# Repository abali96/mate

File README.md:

# mate

Desktop display for live stock market, time, and weather data on a scrolling LED matrix. See http://arjunbali.com/#mate for a full description of the tech, a photo gallery, and a video!

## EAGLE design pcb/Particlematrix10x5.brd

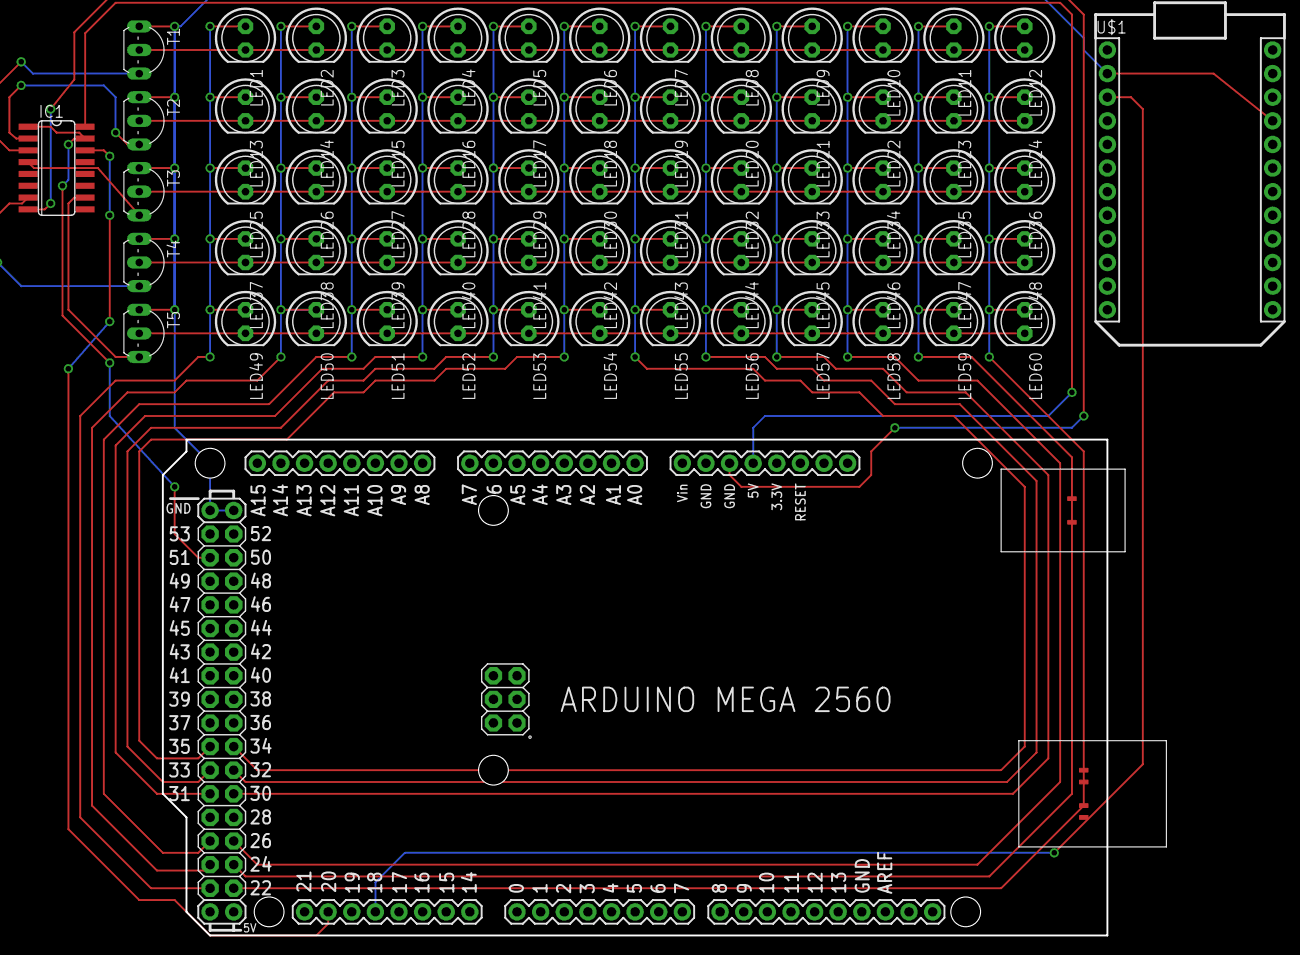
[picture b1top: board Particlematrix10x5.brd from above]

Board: 2 copper layers, 68 parts (0 on the bottom side), 28 nets.

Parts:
IC1: 4017D; SO16
LED1, LED2, LED3, LED4, LED5, LED6, LED7, LED8, LED9, LED10, LED11, LED12, LED13, LED14, LED15, LED16, LED17, LED18, LED19, LED20, LED21, LED22, LED23, LED24, LED25, LED26, LED27, LED28, LED29, LED30, LED31, LED32, LED33, LED34, LED35, LED36, LED37, LED38, LED39, LED40, LED41, LED42, LED43, LED44, LED45, LED46, LED47, LED48, LED49, LED50, LED51, LED52, LED53, LED54, LED55, LED56, LED57, LED58, LED59, LED60: LED5MM
PCB1: ARDUINO_MEGA2560
T1, T2, T3, T4, T5: TO92-EBC
U$1: SPARK_CORECORE; SPARK_CORE

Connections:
COL1: LED1.A, LED13.A, LED25.A, LED37.A, LED49.A, PCB1.23
COL2: LED2.A, LED14.A, LED26.A, LED38.A, LED50.A, PCB1.25
COL3: LED3.A, LED15.A, LED27.A, LED39.A, LED51.A, PCB1.27
COL4: LED4.A, LED16.A, LED28.A, LED40.A, LED52.A, PCB1.31
COL5: LED5.A, LED17.A, LED29.A, LED41.A, LED53.A, PCB1.33
COL6: LED6.A, LED18.A, LED30.A, LED42.A, LED54.A, PCB1.35
COL7: LED7.A, LED19.A, LED31.A, LED43.A, LED55.A, PCB1.34
COL8: LED8.A, LED20.A, LED32.A, LED44.A, LED56.A, PCB1.32
COL9: LED9.A, LED21.A, LED33.A, LED45.A, LED57.A, PCB1.30
COL10: LED10.A, LED22.A, LED34.A, LED46.A, LED58.A, PCB1.26
COL11: LED11.A, LED23.A, LED35.A, LED47.A, LED59.A, PCB1.24
COL12: LED12.A, LED24.A, LED36.A, LED48.A, LED60.A, PCB1.22
GND: PCB1.GND..., PCB1.GND...., T1.E, T2.E, T3.E, T4.E, T5.E, U$1.2, U$1.21
unnamed: IC1.3, T1.C
unnamed: IC1.2, T2.C
unnamed: IC1.4, T3.C
unnamed: IC1.7, T4.C
unnamed: IC1.10, T5.C
unnamed: IC1.16, PCB1.5V
unnamed: IC1.14, PCB1.20
unnamed: IC1.1, IC1.15, PCB1.51
unnamed: IC1.8, PCB1.GND..
unnamed: PCB1.18, U$1.3
ROW1: LED1.K, LED2.K, LED3.K, LED4.K, LED5.K, LED6.K, LED7.K, LED8.K, LED9.K, LED10.K, LED11.K, LED12.K, T1.B
ROW2: LED13.K, LED14.K, LED15.K, LED16.K, LED17.K, LED18.K, LED19.K, LED20.K, LED21.K, LED22.K, LED23.K, LED24.K, T2.B
ROW3: LED25.K, LED26.K, LED27.K, LED28.K, LED29.K, LED30.K, LED31.K, LED32.K, LED33.K, LED34.K, LED35.K, LED36.K, T3.B
ROW4: LED37.K, LED38.K, LED39.K, LED40.K, LED41.K, LED42.K, LED43.K, LED44.K, LED45.K, LED46.K, LED47.K, LED48.K, T4.B
ROW5: LED49.K, LED50.K, LED51.K, LED52.K, LED53.K, LED54.K, LED55.K, LED56.K, LED57.K, LED58.K, LED59.K, LED60.K, T5.B

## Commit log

2015-09-13 added led number configs
2015-09-13 display Test added
    created displayTest, removed false main
2015-09-13 added-hardware-tests
    added tests for the display bitmapping and shift register
2015-09-13 added 4 digit support
2015-09-14 added rain animation
2015-09-14 added more weather
2015-09-14 added weather, numbermap
2015-09-14 Interfaced Spark Core with Arduino
2015-09-14 Merged displayTest code
2015-09-14 added weather mode w 5 states
2015-09-14 Added HTTP client; cleaned up comments
2015-09-15 added button for toggling mode
2015-09-15 Added receiver code for weather
2015-09-15 Able to send weather codes
2015-09-16 Init pcb; added LED matrix schematic
2015-09-16 LED rename
2015-09-17 Added 4017 decade counter to schematic
2015-09-17 Routed all LEDs, decade counter, and Arduino Mega
2015-09-17 Fix routing errors on pcb
2015-09-17 Mirrored Arduino and Spark Core again to face front; rerouted
2015-09-17 Cleanup in schematic
2015-09-17 Renamed brd and sch files
2015-09-17 Create bottle server with basic weather type parsing
2015-09-17 Add time route to return encoded current time
2015-09-17 Formal server running and user location defaulting logic
2015-09-17 Properly adding time offset from utc
2015-09-17 Added procfile
2015-09-17 Added requirements.txt
2015-09-17 Change server port from 8080 to 5000 on environment port
2015-09-17 Remove venv
2015-09-17 Heroku deployment changes
2015-09-17 Move requirements.txt and procfile to root
2015-09-17 Setting api key in environ var
2015-09-17 Remove api keys
2015-09-17 Remove gunicorn
2015-09-17 Set port properly on python server
2015-09-17 Added final weather configs
2015-09-18 Reimplementation of spark core code in order to account for new python backend
2015-09-18 Modify Arduino code to handle spark core data
2015-09-18 Modified return value codes for weather
2015-09-18 Fix in current weather type
2015-09-18 Cleanup in arduino code
2015-09-18 Enforce leading zeros on server side time output
2015-09-18 Separate constants out into separate files for characters, pinouts, and delimiters
2015-09-18 Moved several constant values into separate constants struct
2015-09-18 Refactor weather to remove weatherMap
2015-09-18 Move cloud delay to constants
2015-09-19 Added stock price handling to server side
2015-09-19 Upate pcb trace width to account for print shop limitations
2015-09-19 Fix in weather data constants
2015-09-20 Remapped characters
2015-09-20 Wrote character array concatenation for strings of arbitrary length
2015-09-20 Choppy scrolling text
2015-09-20 Implemented proper scrolling with up to four characters (requires vector data type for more)
2015-09-20 Encoded all standard alphanumerics
2015-09-21 Add punction character LED mappings
2015-09-21 Scrolling text for displays more than 4 charcters long
2015-09-21 Padding text less than 4 characters long for scrolling ability
2015-09-21 Cleanup requirements.txt
2015-09-21 Change route of stock to stocks
2015-09-21 Add stock name to stock price return value
2015-09-21 Remove spaces in stock price
2015-09-21 Add trailing space to stock
2015-09-21 Multiple stock price handling on server side
2015-09-24 Folder rename
2015-09-24 Removed shiftRegTest arduino file
2015-09-24 Update gitignore
2015-09-24 Update to ignore __pycache__
2015-09-24 Remove .DS_Store
2015-09-24 Rename arduino code
2015-09-24 Photon file cleanup
2015-09-24 Cleanup in PCB folder and gitignore for Eagle revisions
